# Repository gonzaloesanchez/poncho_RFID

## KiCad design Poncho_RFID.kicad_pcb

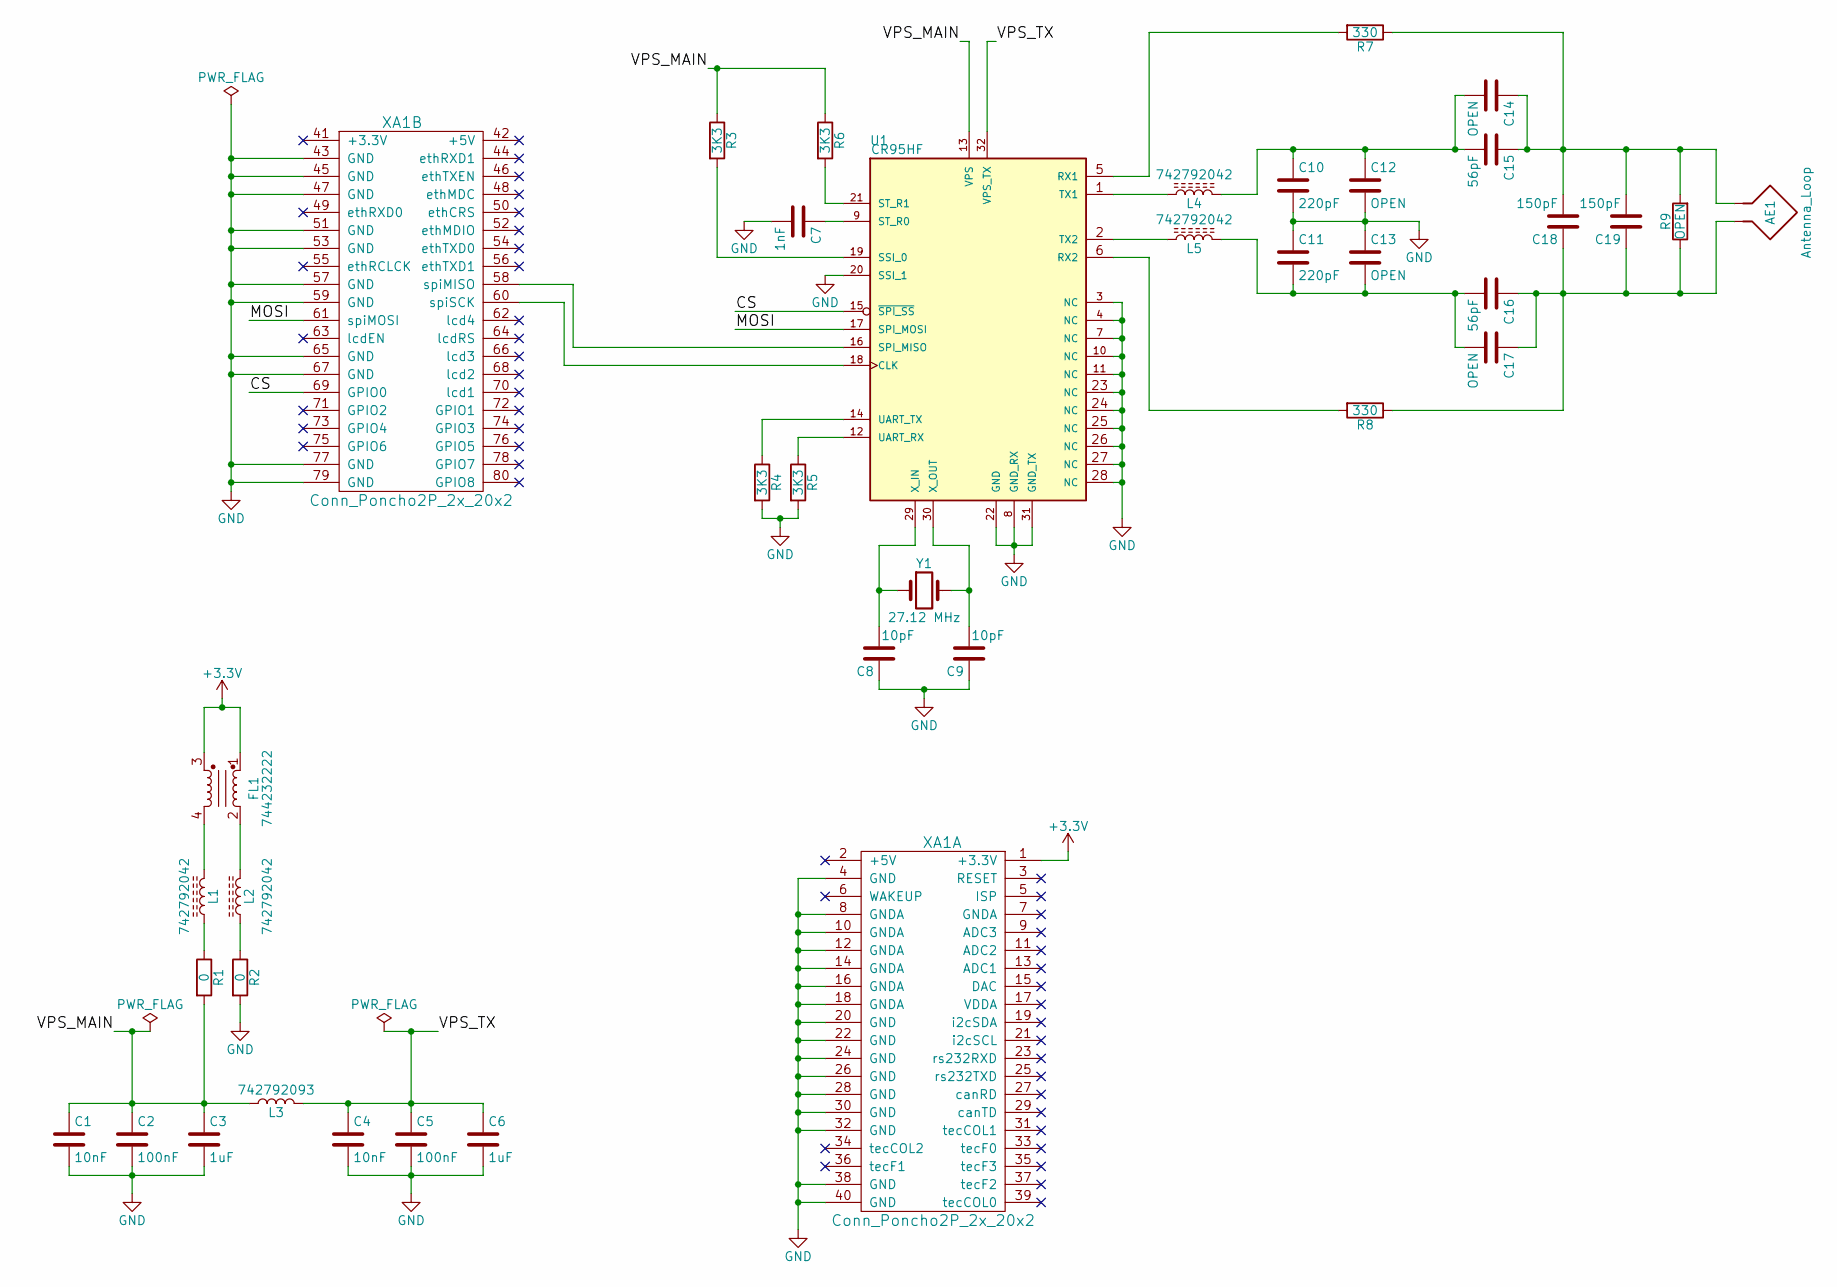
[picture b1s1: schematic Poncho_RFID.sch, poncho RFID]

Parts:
AE1: Antenna_Loop
C1, C4: 10nF; C_0805_HandSoldering; Digikey# 311-1136-1-ND
C2, C5: 100nF; C_0805_HandSoldering; Digikey# 478-1395-1-ND
C3, C6: 1uF; Digikey# 311-1365-1-ND
C7: 1nF; C_0805_HandSoldering; Digikey# 399-1147-1-ND
C8, C9: 10pF; C_0805_HandSoldering; Digikey# 399-7062-1-ND
C10, C11: 220pF; C_0805_HandSoldering; Digikey# 712-1398-1-ND
C12, C13, C14, C17: OPEN; C_0805_HandSoldering
C15, C16: 56pF; C_0805_HandSoldering; Digikey# 1276-1833-1-ND
C18, C19: 150pF; C_0805_HandSoldering; Digikey# 399-1125-1-ND
FL1: 744232222; L_CommonMode_Wuerth_WE-SL2; Digikey# 732-1474-1-ND
L1, L2, L4, L5: 742792042; L_0805_HandSoldering; Digikey# 732-4642-1-ND
L3: 742792093; L_0805_HandSoldering
R1, R2: 0; R_1206_HandSoldering; Digikey# RCL0.0CCT-ND
R3, R4, R5, R6: 3K3; R_0805_HandSoldering; Digikey# RHM3.3KBUCT-ND
R7, R8: 330; R_0805_HandSoldering; Digikey# RHM1215CT-ND
R9: OPEN; R_0805_HandSoldering
U1: CR95HF; QFN-32-1EP_5x5mm_Pitch0.5mm; Digikey# 497-15737-1-ND
XA1: Conn_Poncho2P_2x_20x2; Conn_Poncho_Chico
Y1: 27.12 MHz; Crystal_SMD_5032-2pin_5.0x3.2mm; Digikey# 887-1755-1-ND

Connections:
+3V3: FL1.1, FL1.3, XA1.1 (+3.3V)
/CS: U1.15 (~SPI_SS), XA1.69 (GPIO0)
/MOSI: U1.17 (SPI_MOSI), XA1.61 (spiMOSI)
/VPS_MAIN: C1.1, C2.1, C3.1, L3.2, R1.2, R3.1, R6.1, U1.13 (VPS)
/VPS_TX: C4.1, C5.1, C6.1, L3.1, U1.32 (VPS_TX)
GND: C1.2, C2.2, C3.2, C4.2, C5.2, C6.2, C7.2, C8.1, C9.1, C10.2, C11.1, C12.2, C13.1, R2.2, R4.2, R5.2, U1.3 (NC), U1.4 (NC), U1.7 (NC), U1.8 (GND_RX), U1.10 (NC), U1.11 (NC), U1.20 (SSI_1), U1.22 (GND), U1.23 (NC), U1.24 (NC), U1.25 (NC), U1.26 (NC), U1.27 (NC), U1.28 (NC), U1.31 (GND_TX), XA1.4 (GND), XA1.8 (GNDA), XA1.10 (GNDA), XA1.12 (GNDA), XA1.14 (GNDA), XA1.16 (GNDA), XA1.18 (GNDA), XA1.20 (GND), XA1.22 (GND), XA1.24 (GND), XA1.26 (GND), XA1.28 (GND), XA1.30 (GND), XA1.32 (GND), XA1.38 (GND), XA1.40 (GND), XA1.43 (GND), XA1.45 (GND), XA1.47 (GND), XA1.51 (GND), XA1.53 (GND), XA1.57 (GND), XA1.59 (GND), XA1.65 (GND), XA1.67 (GND), XA1.77 (GND), XA1.79 (GND)
unnamed: AE1.1, C14.1, C15.1, C18.2, C19.2, R7.1, R9.2
unnamed: AE1.2, C16.1, C17.1, C18.1, C19.1, R8.1, R9.1
unnamed: C7.1, U1.9 (ST_R0)
unnamed: C8.2, U1.29 (X_IN), Y1.1
unnamed: C9.2, U1.30 (X_OUT), Y1.2
unnamed: C10.1, C12.1, C14.2, C15.2, L4.1
unnamed: C11.2, C13.2, C16.2, C17.2, L5.1
unnamed: FL1.2, L2.1
unnamed: FL1.4, L1.1
unnamed: L1.2, R1.1
unnamed: L2.2, R2.1
unnamed: L4.2, U1.1 (TX1)
unnamed: L5.2, U1.2 (TX2)
unnamed: R3.2, U1.19 (SSI_0)
unnamed: R4.1, U1.14 (UART_TX)
unnamed: R5.1, U1.12 (UART_RX)
unnamed: R6.2, U1.21 (ST_R1)
unnamed: R7.2, U1.5 (RX1)
unnamed: R8.2, U1.6 (RX2)
unnamed: U1.16 (SPI_MISO), XA1.58 (spiMISO)
unnamed: U1.18 (CLK), XA1.60 (spiSCK)

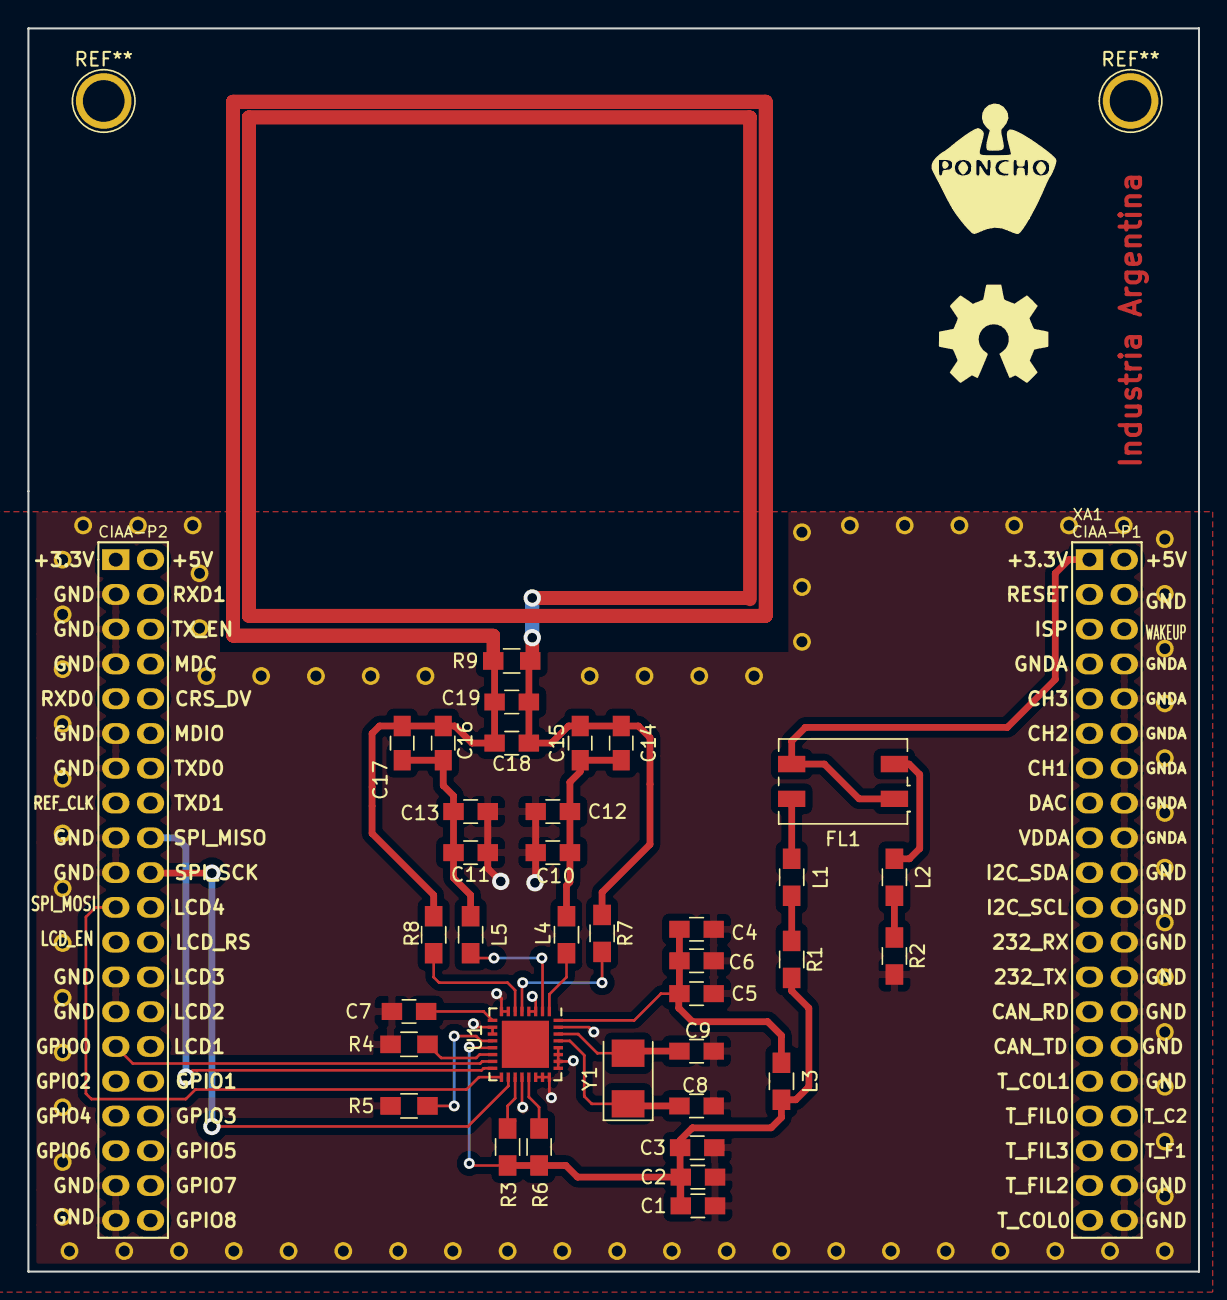
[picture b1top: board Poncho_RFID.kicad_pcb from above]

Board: 2 copper layers, 85.5 x 90.8 mm, 38 parts (0 on the bottom side), 27 nets.

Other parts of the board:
G101: Logo_OSHWA

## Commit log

2017-09-21 Commit Inicial. Inicio de repositorio
2017-09-23 Agregada libreria CR95HF
    Se creo la libreria que contiene el esquematico del CR95HF y se hicieron modificaciones menores en los esquematicos
2017-09-30 Actualizado eeschema
    Circuito alrededor del integrado completo
2017-10-01 Prueba despues del error de MEGAsync
    Este commit hay que hacerle un rebase
2017-10-01 Reestructuracion de esquematico
    Entra todo en una sola pagina, por lo que no hice separacion jerarquica. Actualizados footprints y algunos campos para Kicost
2017-10-14 Actualizacion esquematico
2017-10-28 completado campos kicost
2017-11-11 PCB definido
2017-11-11 Serigrafia ordenada
2017-11-25 Ultimas correcciones
